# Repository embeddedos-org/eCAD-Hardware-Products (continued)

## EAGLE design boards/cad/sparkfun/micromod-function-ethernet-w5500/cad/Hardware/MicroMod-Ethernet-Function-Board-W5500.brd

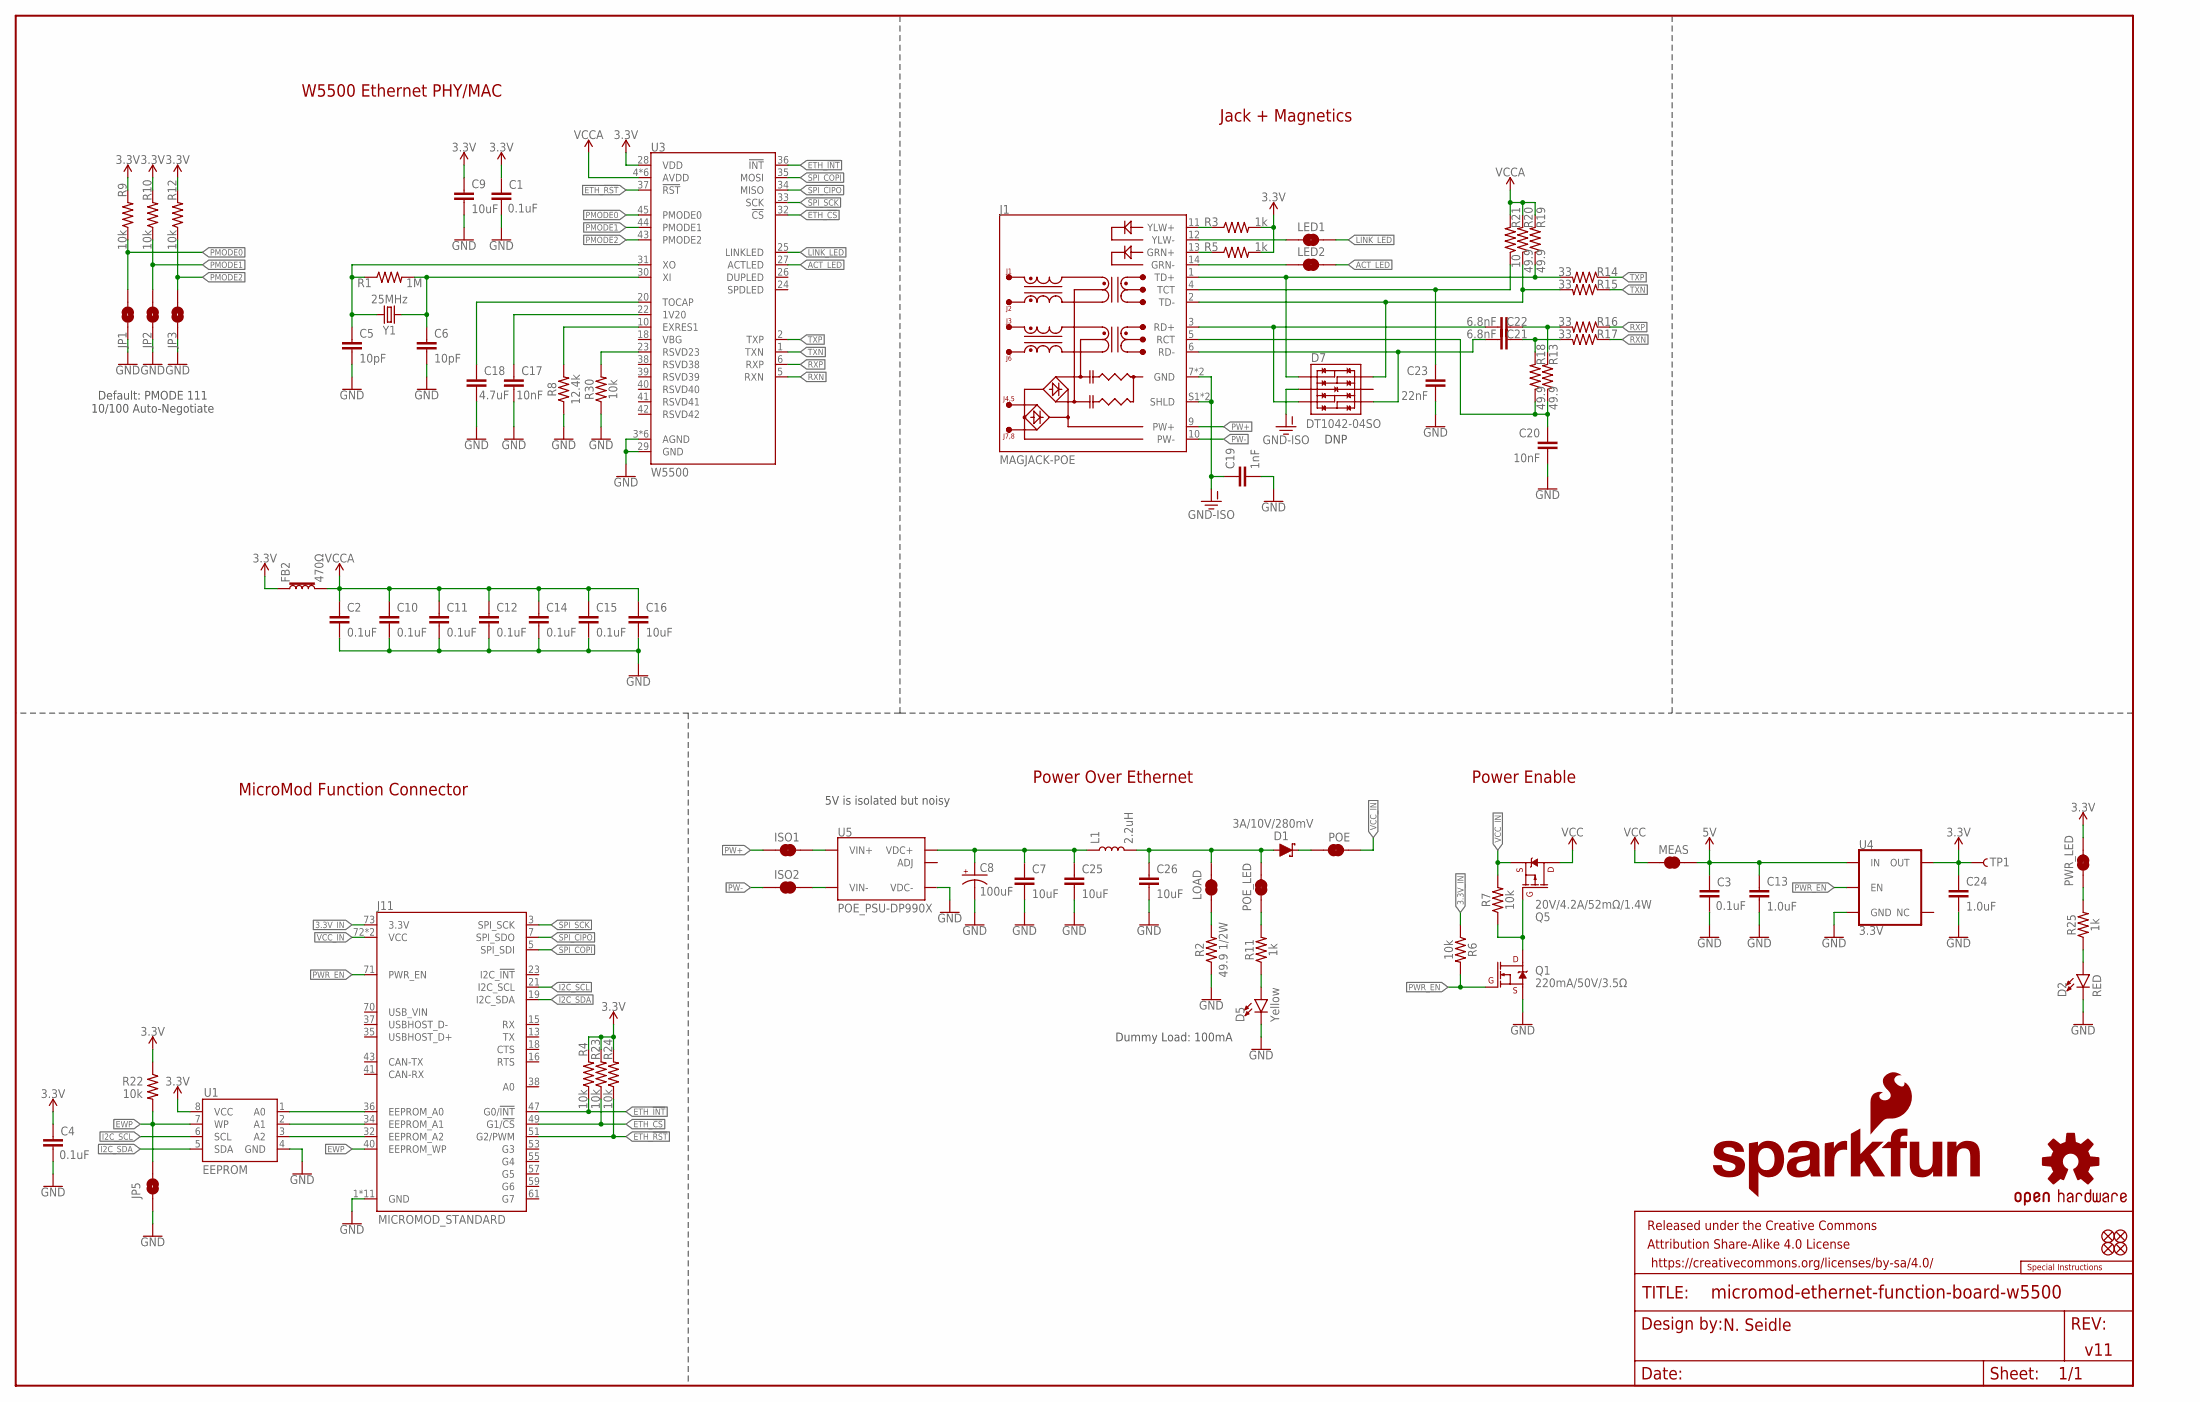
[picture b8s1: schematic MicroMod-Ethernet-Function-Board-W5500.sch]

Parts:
C1, C2, C3, C4, C10, C11, C12, C14, C15: 0.1uF; 0603
C5, C6: 10pF; 0603
C7, C25, C26: 10uF; 0805
C8: 100uF; PANASONIC_D
C9, C16: 10uF; 0603
C13, C24: 1.0uF; 0603
C17, C20: 10nF; 0603
C18: 4.7uF; 0603
C19: 1nF; 1206
C21, C22: 6.8nF; 0603
C23: 22nF; 0603
D1: 3A/10V/280mV; SOD-323
D2: RED; LED-0603
D5: Yellow; LED-0603
D7: DT1042-04SO; SOT-23-6
FB2: 470Ω; 0603
FD1, FD2, FD3, FD4: FIDUCIALUFIDUCIAL; FIDUCIAL-MICRO
FRAME1: FRAME-LEDGER; CREATIVE_COMMONS
ISO1, ISO2: JUMPER-COMBO_2_NC_TRACE; COMBO-JUMPER_2_NC_TRACE
J1: MAGJACK-POE; MAGJACK-SYM_LED
J11: MICROMOD_STANDARD; M.2-CARD-E-22_FUNCTION_STANDARD
JP1, JP2, JP3, JP5: JUMPER-SMT_2_NO_SILK; SMT-JUMPER_2_NO_SILK
L1: 2.2uH; 0805-WIDE
LED1, LED2: JUMPER-SMT_2_NC_TRACE_SILK; SMT-JUMPER_2_NC_TRACE_SILK
LOAD: JUMPER-SMT_2_NC_TRACE_SILK; SMT-JUMPER_2_NC_TRACE_SILK
LOGO1: SFE_LOGO_NAME_FLAME.1_INCH; SFE_LOGO_NAME_FLAME_.1
LOGO2: SPECIAL_INSTRUCTIONS-ORDERING; ORDERING_INSTRUCTIONS
LOGO3: OSHW-LOGOMINI; OSHW-LOGO-MINI
MEAS: JUMPER-COMBO_2_NC_TRACE; COMBO-JUMPER_2_NC_TRACE
POE: JUMPER-SMT_2_NC_TRACE_SILK; SMT-JUMPER_2_NC_TRACE_SILK
POE_LED: JUMPER-SMT_2_NC_TRACE_SILK; SMT-JUMPER_2_NC_TRACE_SILK
PWR_LED: JUMPER-SMT_2_NC_TRACE_SILK; SMT-JUMPER_2_NC_TRACE_SILK
Q1: 220mA/50V/3.5Ω; SOT23-3
Q5: 20V/4.2A/52mΩ/1.4W; SOT23-3
R1: 1M; 0603
R2: 49.9 1/2W; 1206
R3, R5, R11, R25: 1k; 0603
R4, R6, R7, R9, R10, R12, R22, R23, R24, R30: 10k; 0603
R8: 12.4k; 0603
R13, R18, R19, R20: 49.9; 0603
R14, R15, R16, R17: 33; 0603
R21: 10; 0603
TP1: TEST-POINT3X4; PAD.03X.04
U1: EEPROM; SO08
U3: W5500; LQFP-48
U4: 3.3V; SOT23-5
U5: POE_PSU-DP990X; DP990X
Y1: 25MHz; CRYSTAL-SMD-2.0X1.6MM

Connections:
3.3V: C1.1, C4.1, C9.1, C24.1, FB2.1, PWR_LED.2, R3.2, R4.2, R5.2, R9.2, R10.2, R12.2, R22.1, R23.2, R24.2, TP1.1, U1.8 (VCC), U3.28 (VDD), U4.5 (OUT)
3.3V_IN: J11.73 (3.3V), R6.1
5V: C3.1, C13.1, MEAS.2, MEAS.4 (2), U4.1 (IN)
5V_FILTER: C26.1, D1.A, L1.2, LOAD.2, POE_LED.2
5V_RAW: C7.1, C8.+, C25.1, L1.1, U5.1 (VDC+), U5.2 (VDC+)
A0: J11.36 (EEPROM_A0), U1.1 (A0)
A1: J11.34 (EEPROM_A1), U1.2 (A1)
A2: J11.32 (EEPROM_A2), U1.3 (A2)
ACT_LED: LED2.2, U3.27 (ACTLED)
ETH_!CS!: J11.49 (G1/!CS!), R23.1, U3.32 (!CS!)
ETH_!INT!: J11.47 (G0/!INT!), R4.1, U3.36 (!INT!)
ETH_!RST!: J11.51 (G2/PWM), R24.1, U3.37 (!RST!)
EWP: J11.40 (EEPROM_WP), JP5.2, R22.2, U1.7 (WP)
GND: C1.2, C2.2, C3.2, C4.2, C5.2, C6.2, C7.2, C8.-, C9.2, C10.2, C11.2, C12.2, C13.2, C14.2, C15.2, C16.2, C17.2, C18.2, C19.2, C20.2, C23.2, C24.2, C25.2, C26.2, D2.C, D5.C, J11.1 (GND), J11.33 (GND), J11.39 (GND), J11.45 (GND), J11.75 (GND), J11.GND1 (GND), J11.GND2 (GND), J11.GND3 (GND), J11.GND4 (GND), J11.GND5 (GND), J11.GND6 (GND), JP1.1, JP2.1, JP3.1, JP5.1, Q1.2 (S), R2.1, R8.1, R30.1, U1.4 (GND), U3.3 (AGND), U3.9 (AGND), U3.14 (AGND), U3.16 (AGND), U3.19 (AGND), U3.29 (GND), U3.48 (AGND), U4.2 (GND), U5.3 (VDC-)
GND-ISO: C19.1, D7.2 (VSS), J1.7 (GND), J1.8 (GND), J1.S1 (SHLD), J1.S2 (SHLD)
I2C_SCL: J11.21 (I2C_SCL), U1.6 (SCL)
I2C_SDA: J11.19 (I2C_SDA), U1.5 (SDA)
LINK_LED: LED1.2, U3.25 (LINKLED)
unnamed: C5.1, R1.1, U3.31 (XO), Y1.1
unnamed: C6.1, R1.2, U3.30 (XI), Y1.3 (2)
unnamed: J1.14 (GRN-), LED2.1
unnamed: J1.12 (YLW-), LED1.1
unnamed: D5.A, R11.1
unnamed: POE_LED.1, R11.2
unnamed: D1.C, POE.1
unnamed: J1.13 (GRN+), R5.1
unnamed: LOAD.1, R2.2
unnamed: J1.11 (YLW+), R3.1
unnamed: Q1.3 (D), Q5.1 (G), R7.1
unnamed: R8.2, U3.10 (EXRES1)
unnamed: C17.1, U3.22 (1V20)
unnamed: C18.1, U3.20 (TOCAP)
unnamed: R30.2, U3.23 (RSVD23)
unnamed: PWR_LED.1, R25.2
unnamed: D2.A, R25.1
PMODE0: JP1.2, R9.1, U3.45 (PMODE0)
PMODE1: JP2.2, R10.1, U3.44 (PMODE1)
PMODE2: JP3.2, R12.1, U3.43 (PMODE2)
PW1+: ISO1.2, ISO1.4 (2), U5.5 (VIN+), U5.6 (VIN+)
PW1-: ISO2.2, ISO2.4 (2), U5.7 (VIN-), U5.8 (VIN-)
PW+: ISO1.1, ISO1.3 (1), J1.9 (PW+)
PW-: ISO2.1, ISO2.3 (1), J1.10 (PW-)
PWR_EN: J11.71 (PWR_EN), Q1.1 (G), R6.2, U4.3 (EN)
RCT: C20.1, J1.5 (RCT), R13.1, R18.1
RD+: C22.2, D7.3 (IO2), J1.3 (RD+)
RD-: C21.2, D7.4 (IO3), J1.6 (RD-)
RXN: R17.1, U3.5 (RXN)
RXN1: C21.1, R17.2, R18.2
RXP: R16.1, U3.6 (RXP)
RXP1: C22.1, R13.2, R16.2
SPI_CIPO: J11.7 (SPI_SDO), U3.34 (MISO)
SPI_COPI: J11.5 (SPI_SDI), U3.35 (MOSI)
SPI_SCK: J11.3 (SPI_SCK), U3.33 (SCK)
TCT: C23.1, J1.4 (TCT), R21.1
TD+: D7.1 (IO1), J1.1 (TD+), R14.2, R19.1
TD-: D7.6 (IO4), J1.2 (TD-), R15.2, R20.1
TXN: R15.1, U3.1 (TXN)
TXP: R14.1, U3.2 (TXP)
VCC: MEAS.1, MEAS.3 (1), Q5.3 (D)
VCCA: C2.1, C10.1, C11.1, C12.1, C14.1, C15.1, C16.1, FB2.2, R19.2, R20.2, R21.2, U3.4 (AVDD), U3.8 (AVDD), U3.11 (AVDD), U3.15 (AVDD), U3.17 (AVDD), U3.21 (AVDD)
VCC_IN: J11.72 (VCC), J11.74 (VCC), POE.2, Q5.2 (S), R7.2

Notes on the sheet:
Power Over Ethernet
MicroMod Function Connector
5V is isolated but noisy
N. Seidle
v11
W5500 Ethernet PHY/MAC
Power Enable
Default: PMODE 111 10/100 Auto-Negotiate
Jack + Magnetics
Dummy Load: 100mA
DNP

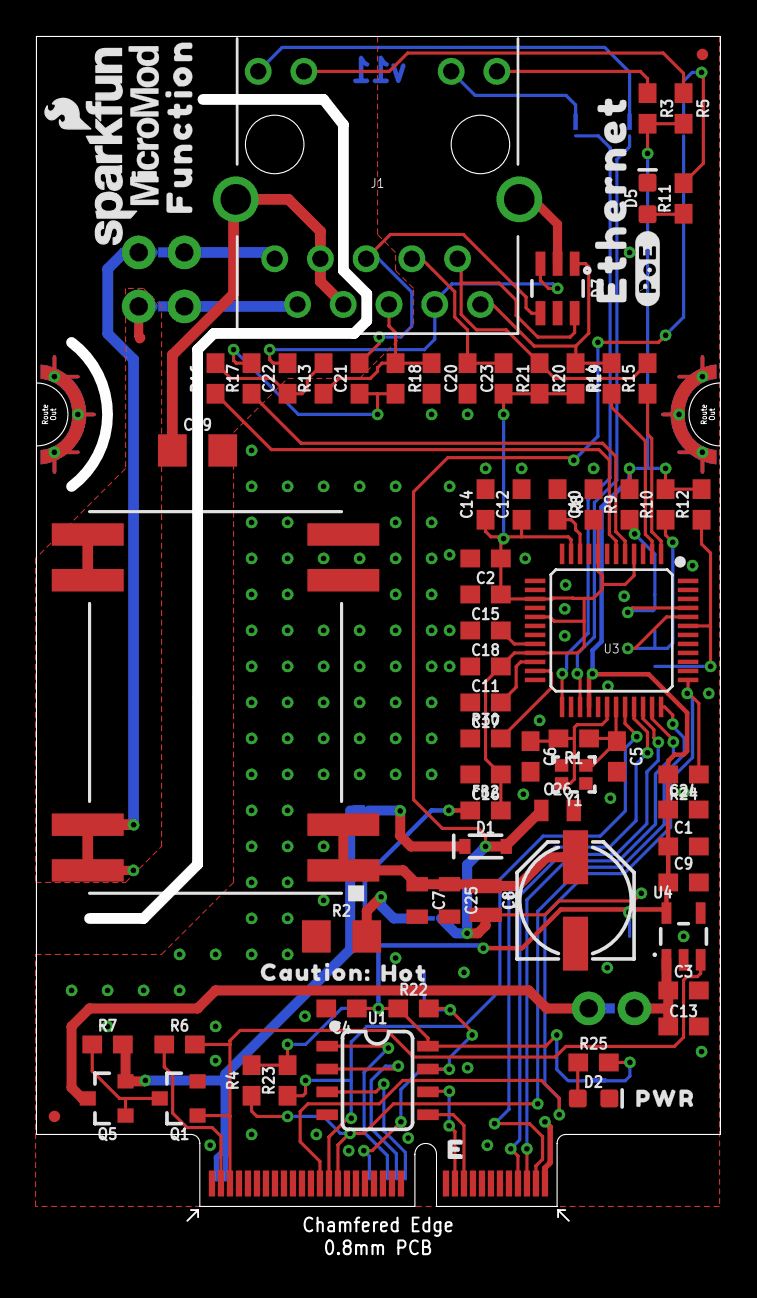
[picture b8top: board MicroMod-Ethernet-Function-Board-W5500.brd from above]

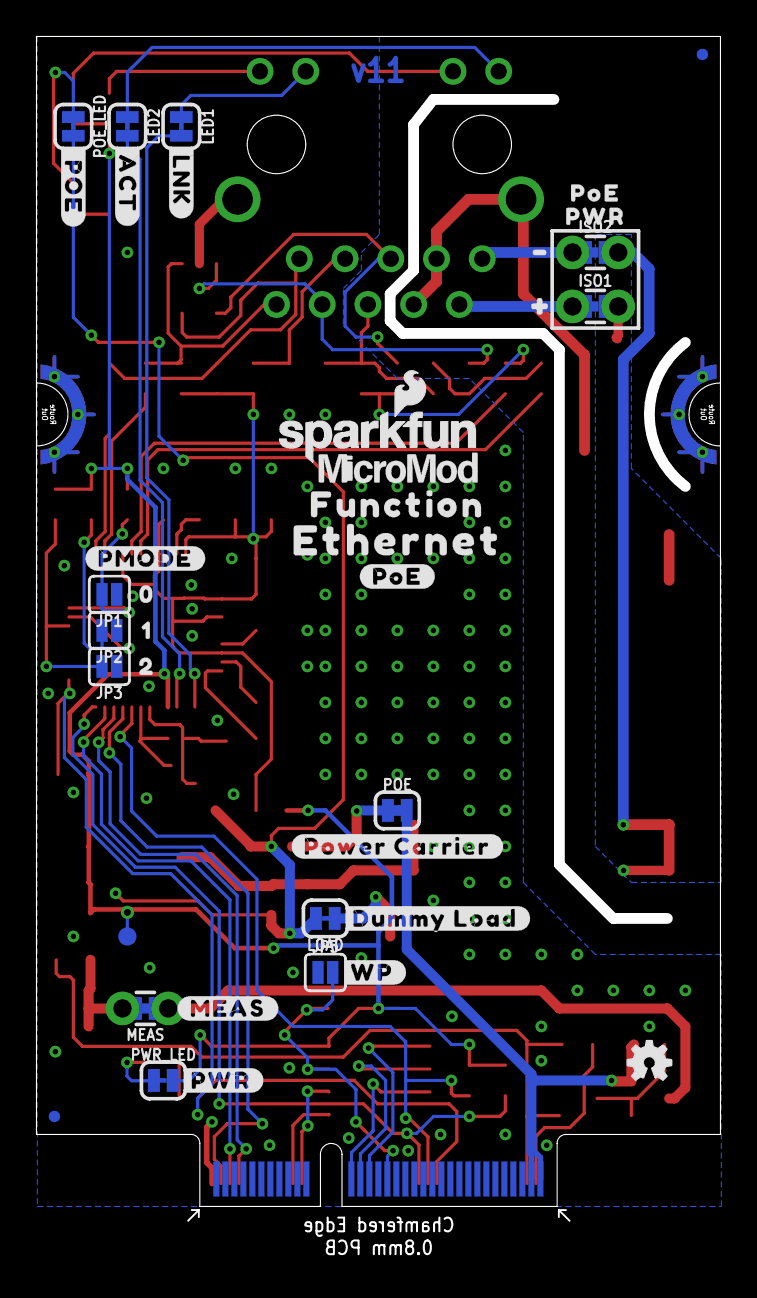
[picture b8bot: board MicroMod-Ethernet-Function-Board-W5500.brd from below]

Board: 2 copper layers, 38.0 x 65.8 mm, 117 parts (38 on the bottom side), 61 nets.

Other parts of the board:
LOGO4: SFE_LOGO_NAME_FLAME.1_INCH; SFE_LOGO_NAME_FLAME_.1
U$1, U$17: ETHERNET0
U$2, U$18: #POE#0
U$3: #POWER_CARRIER#0
U$5: #DUMMY_LOAD#0
U$6: #WP#0
U$7: PWR0
U$8: #ACT#0
U$9: POE0
U$12: #LNK#1
U$13: #PMODE#0
U$14: 01
U$15: 12
U$16: 23
U$19: #0
U$20: CAUTION#0
U$21: HOT#1
U$22: #PWR#0
U$23: #_POE#0
U$24: PWR1
U$25: #1
U$26, U$27: FUNCTION0
U$28: #MEAS#3
U$37, U$63: MICROMOD_LOGO_.35

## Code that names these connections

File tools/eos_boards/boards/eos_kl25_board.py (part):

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  the KL25's, and its single-chip USB (no crystal). TXD and RXD meet D0/D1 through 1 kohm, so a
  shield driving D0 against the bridge's TXD fights at most 3.3 mA, within its 6.5 mA
  low-drive rating (Table 3.7); 1 kohm x about 20 pF = 20 ns is nothing at 3 Mbaud.
* RGB LED: Wurth 150141M173100 (common anode; pin 1 anode, 2 blue, 3 red, 4 green). VF at
  20 mA: red 2.0 V typ (2.4 max), green and blue 3.2 V typ (3.6 max), 30 mA continuous max.
  From 3.3 V a GPIO cannot light green or blue reliably (3.6 V max), so the anode is on 5 V and
  each colour is switched by an AO3400A N-MOSFET (Alpha & Omega: VGS(th) 0.65-1.45 V, RDS(on)
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# body, then pad 7 down to the 100 uF.
PRIORITY = [(("U3", "2"), ("U3", "7")), (("U3", "7"), ("C3", "1"))]
# The accelerometer's two interrupt lines (U7 pins 11 and 12, side by side at 0.5 mm) go first,
# INT2 then INT1: they leave the package in the same order they reach the MCU (pins 77 and 80), and
# laid before the plane fan-out, neither one's via can land in front of the other's pad. SA0 (pin 3
# to JP2) is next, while the south side of that pad is still open. Pins 2 and 9 are both +3V3, but
# a 0.3 mm track cannot leave either (the neighbours are 0.5 mm away and the maze's margin closes
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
